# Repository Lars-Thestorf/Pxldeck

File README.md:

# Pxldeck

DIY Handheld Games Console with an 32x64 Led Matrix driven by ESP32.

The Display is an P3 HUB75 LedMatrix Module.
Lots of this Modules are usally used in Advertisement Panels.
The Case is entirely 3D printed.

## Features
- 32x64 pixel screen which can be stupidly bright
- 15 buttons and two analog sticks as input
- 3000mAh battery which lasts like 10 hours
- ESP32 microcontroller providing WiFi Capabilitys, does all the gameplay processing and is driving the Screen
- ATXMega microcontroller doing battery management and input handling since the ESP just hasn't enough pins for all of that. It also serves as an USB to Uart converter so the consoles software can be updated just by plugging it into the PC.
- This Repo also contains an "Emulator" to run the games code on PC.

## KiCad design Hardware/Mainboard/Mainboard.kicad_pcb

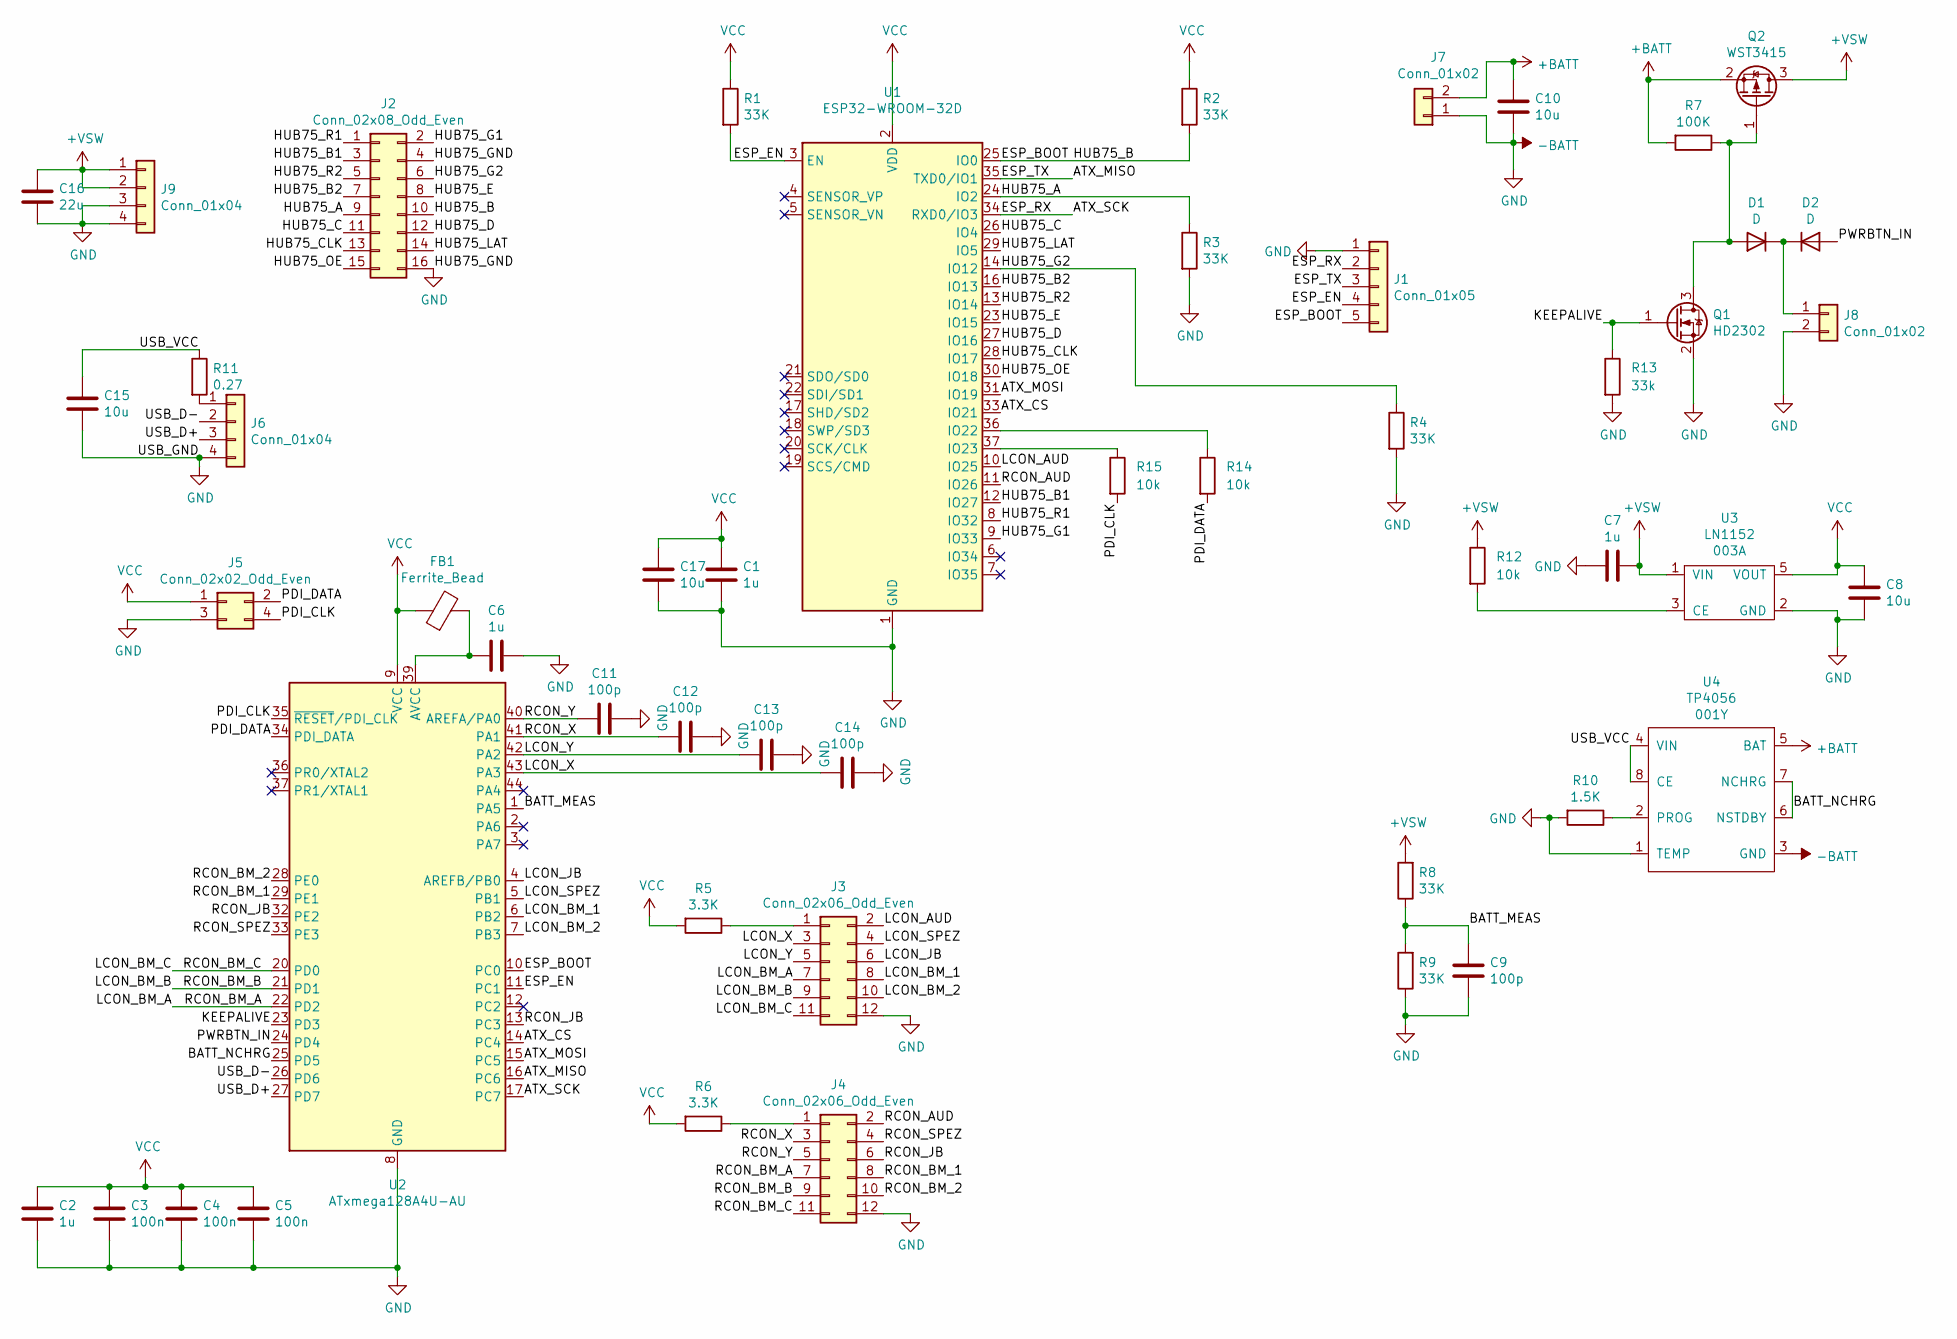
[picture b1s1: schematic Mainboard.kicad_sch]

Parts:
C1, C2, C6, C7: 1u; C_0402_1005Metric
C3, C4, C5: 100n; C_0402_1005Metric
C8: 10u; C_0805_2012Metric
C9, C11, C12, C13, C14: 100p; C_0402_1005Metric
C10, C15: 10u; C_0603_1608Metric
C16: 22u; C_1206_3216Metric
C17: 10u; C_1210_3225Metric
D1, D2: D; D_0603_1608Metric
FB1: Ferrite_Bead; L_0603_1608Metric
J1: Conn_01x05; PinHeader_1x05_P1.27mm_Vertical
J2: Conn_02x08_Odd_Even; PinSocket_2x08_P2.54mm_Vertical
J3, J4: Conn_02x06_Odd_Even; PinHeader_2x06_P2.54mm_Horizontal
J5: Conn_02x02_Odd_Even; PinHeader_2x02_P2.54mm_Vertical
J6, J9: Conn_01x04; PinHeader_1x04_P2.54mm_Vertical
J7, J8: Conn_01x02; PinHeader_1x02_P2.54mm_Vertical
Q1: HD2302; SOT-23
Q2: WST3415; TSOT-23
R1, R2, R3, R4, R8, R9: 33K; R_0402_1005Metric
R5, R6: 3.3K; R_0402_1005Metric
R7: 100K; R_0402_1005Metric
R10: 1.5K; R_0402_1005Metric
R11: 0.27; R_0805_2012Metric
R12, R14, R15: 10k; R_0402_1005Metric
R13: 33k; R_0402_1005Metric
U1: ESP32-WROOM-32D; ESP32-WROOM-32E
U2: ATxmega128A4U-AU; TQFP-44_10x10mm_P0.8mm
U3: LN1152; SOT-23-5
U4: TP4056; HSOP-8-1EP_3.9x4.9mm_P1.27mm_EP2.41x3.1mm_ThermalVias

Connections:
+BATT: C10.1, J7.2, Q2.2 (S), R7.2, U4.5 (BAT)
+VSW: C7.1, C16.1, J9.1, J9.2, Q2.3 (D), R8.2, R12.1, U3.1 (VIN)
-BATT: C1.2, C2.2, C3.2, C4.2, C5.2, C6.1, C7.2, C8.2, C9.2, C10.2, C11.1, C12.1, C13.1, C14.1, C15.2, C16.2, C17.2, J1.1, J2.4, J2.16, J3.12, J4.12, J5.3, J6.4, J7.1, J8.2, J9.3, J9.4, Q1.2 (S), R3.2, R4.2, R9.1, R10.2, R13.2, U1.1 (GND), U1.15 (GND), U1.38 (GND), U1.39 (GND), U2.8 (GND), U2.18 (GND), U2.30 (GND), U2.38 (GND), U3.2 (GND), U4.1 (TEMP), U4.3 (GND), U4.9 (GND)
/ATX_CS: U1.33 (IO21), U2.14 (PC4)
/ATX_MISO: J1.3, U1.35 (TXD0/IO1), U2.16 (PC6)
/ATX_MOSI: U1.31 (IO19), U2.15 (PC5)
/ATX_SCK: J1.2, U1.34 (RXD0/IO3), U2.17 (PC7)
/BATT_MEAS: C9.1, R8.1, R9.2, U2.1 (PA5)
/BATT_NCHRG: U2.25 (PD5), U4.6 (NSTDBY), U4.7 (NCHRG)
/ESP_BOOT: J1.5, J2.10, R2.2, U1.25 (IO0), U2.10 (PC0)
/ESP_EN: J1.4, R1.2, U1.3 (EN), U2.11 (PC1)
/HUB75_A: J2.9, R3.1, U1.24 (IO2)
/HUB75_B1: J2.3, U1.12 (IO27)
/HUB75_B2: J2.7, U1.16 (IO13)
/HUB75_C: J2.11, U1.26 (IO4)
/HUB75_CLK: J2.13, U1.28 (IO17)
/HUB75_D: J2.12, U1.27 (IO16)
/HUB75_E: J2.8, U1.23 (IO15)
/HUB75_G1: J2.2, U1.9 (IO33)
/HUB75_G2: J2.6, R4.1, U1.14 (IO12)
/HUB75_LAT: J2.14, U1.29 (IO5)
/HUB75_OE: J2.15, U1.30 (IO18)
/HUB75_R1: J2.1, U1.8 (IO32)
/HUB75_R2: J2.5, U1.13 (IO14)
/KEEPALIVE: Q1.1 (G), R13.1, U2.23 (PD3)
/LCON_AUD: J3.2, U1.10 (IO25)
/LCON_BM_1: J3.8, U2.6 (PB2)
/LCON_BM_2: J3.10, U2.7 (PB3)
/LCON_BM_A: J3.7, J4.7, U2.22 (PD2)
/LCON_BM_B: J3.9, J4.9, U2.21 (PD1)
/LCON_BM_C: J3.11, J4.11, U2.20 (PD0)
/LCON_JB: J3.6, U2.4 (AREFB/PB0)
/LCON_SPEZ: J3.4, U2.5 (PB1)
/LCON_X: C14.2, J3.3, U2.43 (PA3)
/LCON_Y: C13.2, J3.5, U2.42 (PA2)
/PDI_CLK: J5.4, R15.2, U2.35 (~RESET/PDI_CLK)
/PDI_DATA: J5.2, R14.2, U2.34 (PDI_DATA)
/PWRBTN_IN: D2.2 (A), U2.24 (PD4)
/RCON_AUD: J4.2, U1.11 (IO26)
/RCON_BM_1: J4.8, U2.29 (PE1)
/RCON_BM_2: J4.10, U2.28 (PE0)
/RCON_JB: J4.6, U2.13 (PC3), U2.32 (PE2)
/RCON_SPEZ: J4.4, U2.33 (PE3)
/RCON_X: C12.2, J4.3, U2.41 (PA1)
/RCON_Y: C11.2, J4.5, U2.40 (AREFA/PA0)
/USB_D+: J6.3, U2.27 (PD7)
/USB_D-: J6.2, U2.26 (PD6)
/USB_VCC: C15.1, R11.1, U4.4 (VIN), U4.8 (CE)
unnamed: C6.2, FB1.2, U2.39 (AVCC)
unnamed: D1.1 (K), D2.1 (K), J8.1
unnamed: D1.2 (A), Q1.3 (D), Q2.1 (G), R7.1
unnamed: J3.1, R5.1
unnamed: J4.1, R6.1
unnamed: J6.1, R11.2
unnamed: R10.1, U4.2 (PROG)
unnamed: R14.1, U1.36 (IO22)
unnamed: R15.1, U1.37 (IO23)
unnamed: R12.2, U3.3 (CE)
VCC: C1.1, C2.1, C3.1, C4.1, C5.1, C8.1, C17.1, FB1.1, J5.1, R1.1, R2.1, R5.2, R6.2, U1.2 (VDD), U2.9 (VCC), U2.19 (VCC), U2.31 (VCC), U3.5 (VOUT)

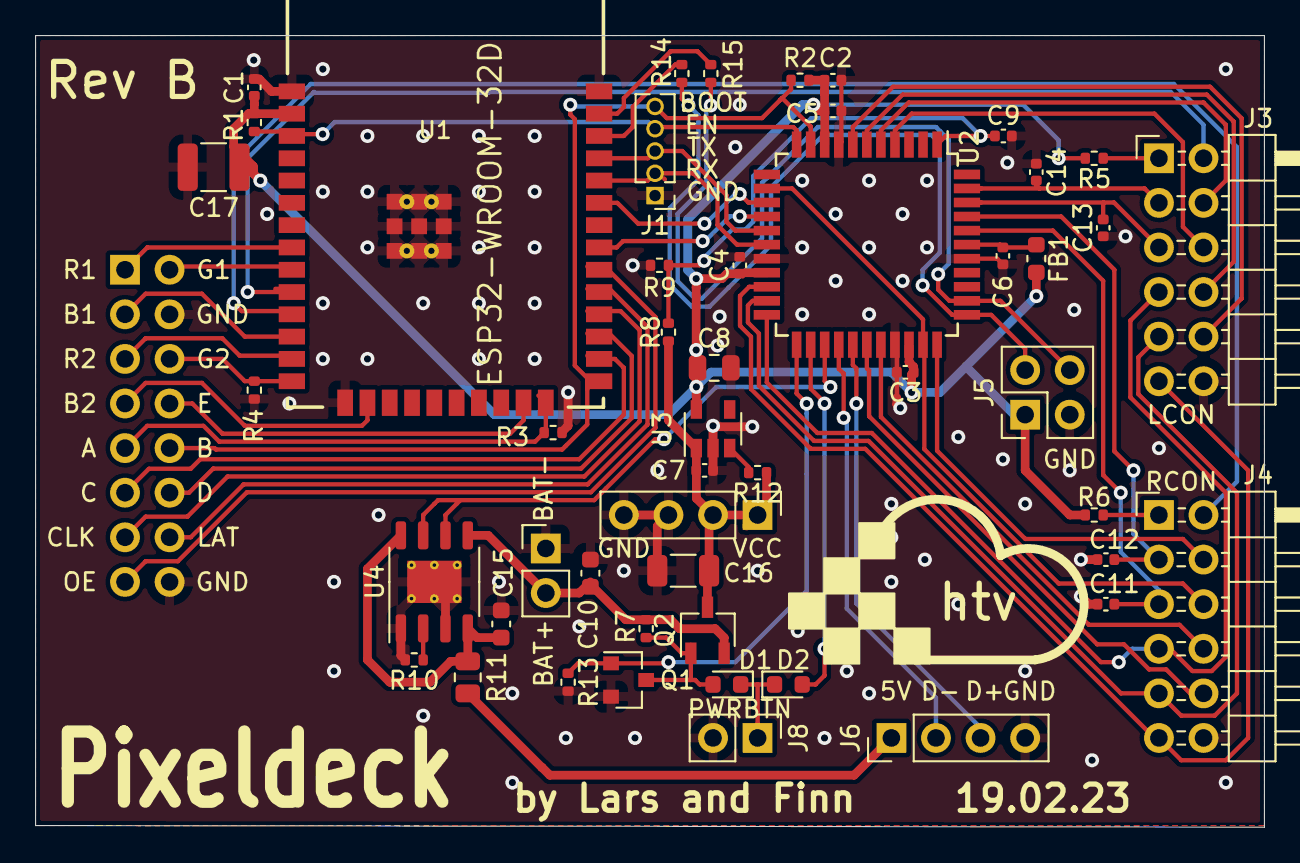
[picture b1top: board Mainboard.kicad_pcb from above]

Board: 2 copper layers, 70.0 x 45.1 mm, 50 parts (1 on the bottom side), 59 nets.

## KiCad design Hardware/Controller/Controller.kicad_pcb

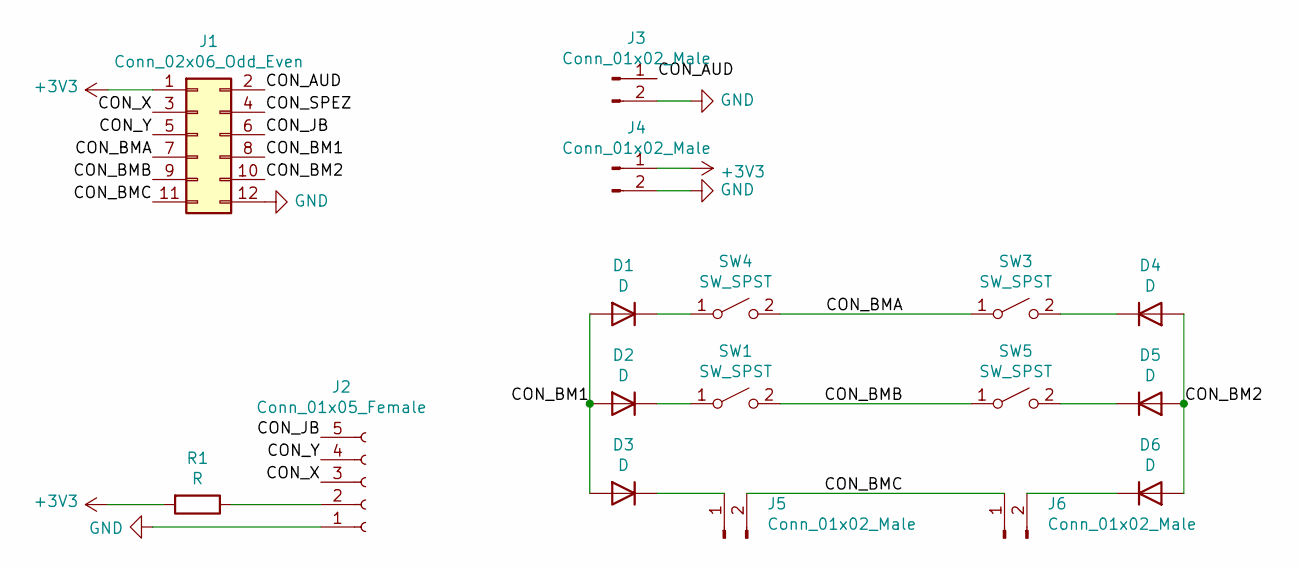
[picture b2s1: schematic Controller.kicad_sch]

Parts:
D1, D2, D3, D4, D5, D6: D; D_SOD-123
J1: Conn_02x06_Odd_Even; PinHeader_2x06_P2.54mm_Horizontal
J2: Conn_01x05_Female; PinSocket_1x05_P2.54mm_Horizontal
J3, J4: Conn_01x02_Male; PinHeader_1x02_P2.54mm_Vertical
J5, J6: Conn_01x02_Male; PinHeader_1x02_P2.54mm_Horizontal
R1: R; R_0402_1005Metric
SW1, SW3, SW4, SW5: SW_SPST; SW_SPST_B3S-1000

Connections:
+3V3: J1.1, J4.1, R1.2
/CON_AUD: J1.2, J3.1
/CON_BM1: D1.2 (A), D2.2 (A), D3.2 (A), J1.8
/CON_BM2: D4.2 (A), D5.2 (A), D6.2 (A), J1.10
/CON_BMA: J1.7, SW3.1 (A), SW4.2 (B)
/CON_BMB: J1.9, SW1.2 (B), SW5.1 (A)
/CON_BMC: J1.11, J5.2, J6.1
/CON_JB: J1.6, J2.5
/CON_SPEZ: J1.4
/CON_X: J1.3, J2.3
/CON_Y: J1.5, J2.4
GND: J1.12, J2.1, J3.2, J4.2
unnamed: D1.1 (K), SW4.1 (A)
unnamed: D2.1 (K), SW1.1 (A)
unnamed: D3.1 (K), J5.1
unnamed: D4.1 (K), SW3.2 (B)
unnamed: D5.1 (K), SW5.2 (B)
unnamed: D6.1 (K), J6.2
unnamed: J2.2, R1.1

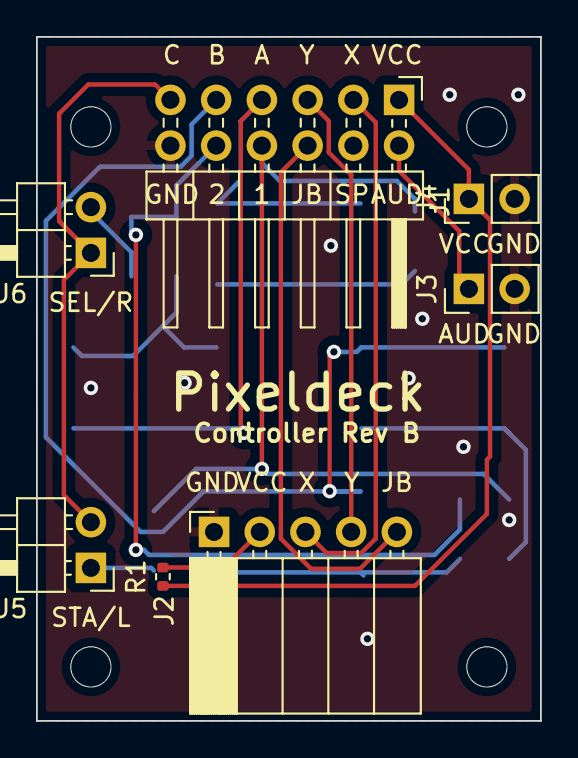
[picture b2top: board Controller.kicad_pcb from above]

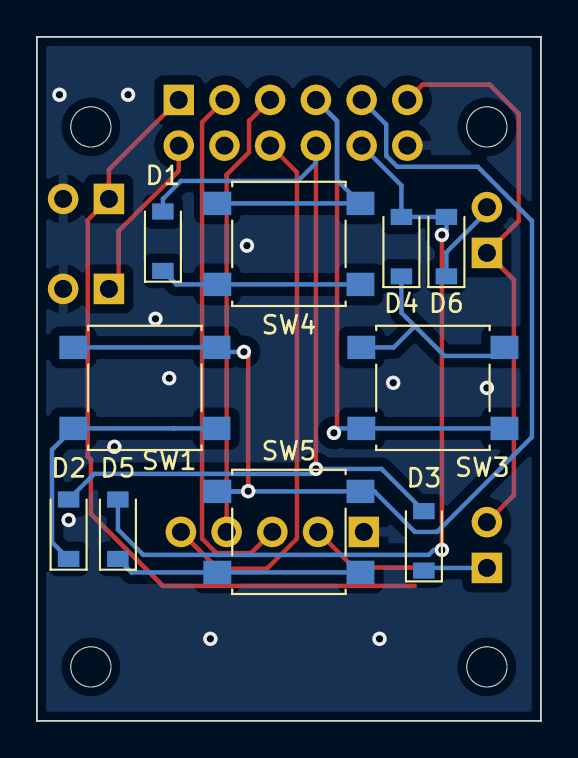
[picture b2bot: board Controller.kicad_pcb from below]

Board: 2 copper layers, 28.0 x 38.0 mm, 17 parts (10 on the bottom side), 18 nets.

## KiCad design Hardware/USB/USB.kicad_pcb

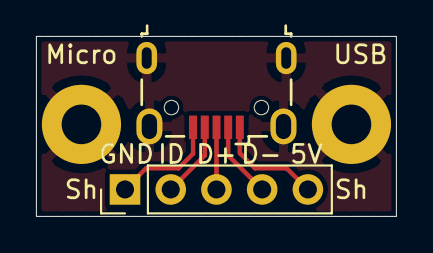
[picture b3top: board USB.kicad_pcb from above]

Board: 2 copper layers, 20.0 x 10.0 mm, 4 parts (0 on the bottom side), 6 nets.

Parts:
H1, H2: MountingHole_Pad; MountingHole_2.2mm_M2_Pad
J1: USB_OTG; USB_Micro-B_Wuerth_629105150521
J2: Conn_01x05_Male; PinHeader_1x05_P2.54mm_Vertical

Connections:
/5V: J1.1, J2.5
/D+: J1.3, J2.3
/D-: J1.2, J2.4
/GND: J1.5, J2.1
/ID: J1.4, J2.2
/Shield: H1.1, H2.1, J1.6

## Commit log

2021-08-07 Initial commit2
2021-08-08 power management
2021-08-10 finetuning
2021-08-10 fixing
2021-08-15 Mainboard finished?
2021-08-16 more powerfull main pfet
2021-09-04 add case and code
2021-09-05 bootlogo
2021-09-06 xmega as hackyprog
2021-09-10 xmega software
2021-09-11 uart comm
2021-09-12 button comm working
2021-09-12 kleinigkeit
2021-09-15 first working state of main menu
2021-09-18 first working state with pong
2021-09-18 new power button interrupt
2021-09-21 fix USB issues
2021-09-25 make pong more fun and joystick calibration
2021-09-27 draw Image function
2021-09-27 make lufa an actual submodule
2021-09-29 Multiplayer
2021-10-08 Teeetrrriiiiisss
2021-10-10 better tetris
2021-11-15 Add controller PCB
2021-11-19 highscore list
2021-11-21 Changes related to new Controller pcb#
2021-12-18 start refactoring for getting emulator to work
2021-12-19 still hacky but working tetris on emu
2021-12-24 worked on porting
2022-01-15 add sokoban game
2022-01-15 small sokoban bugfix update
2022-08-05 sokoban bugfixes, attempt flimmer reduction
2022-11-10 lots of rework on HMatrix software architecture
2022-12-11 new button tolerances
2022-12-11 Add README.md
2023-01-07 add power button to case
2023-01-18 snake
2023-01-20 websocketserver, not working yet
2023-01-21 wifi starts webserver not wörking
2023-01-31 wie viele Sokuban Level willst du? - Ja. xD
2023-01-31 small Sokoban changes
2023-01-31 Lars will alten progress fix
2023-01-31 bug vielleicht gefixt
2023-01-31 add game icons
2023-02-01 green border when soko world finisched
2023-02-01 andere Variante für websocketserver. Irgendwas mit cmake falsch. Komponente wird erkannt und gebaut, hab aber eine undifined reference. Komponente wird nicht in die main gelinked. Weis nicht wie man 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
2023-02-01 add highscore to tetris
2023-02-02 Tetris auch mit A startbar
2023-02-04 change playerinput. Emulator changes for playerinput needed
2023-02-04 settingsmenu
2023-02-05 fix emulator and new input handling
2023-02-05 fix redshift and brightness settings
2023-02-05 Nach homebutton press, wird nicht menü geöffnet
2023-02-06 Accounts gehen soweit. Emulator braucht 2 storage Funktionen für Strings. Finn hat schon wieder Emulator zerstört. :/
2023-02-07 Higscores in Tetris mit namen! Merkwürdiger bug. Speichert nur namen bis 2 zeichen oder kann nur namen mit 2 zeichen lesen
2023-02-07 weiter probiert,aber gelicher Felher. bin ratlos
2023-02-07 implement string storage functions for emulator
2023-02-07 sankegame step to mp
2023-02-09 i dont know
2023-02-10 start working on tetris multiplayer
2023-02-12 change tetris structure
2023-02-12 tetris multiplayer almost playable
2023-02-14 start to implement rotation
2023-02-19 rev 2 Hw
2023-03-23 Rename Project in readme
2023-04-02 improve controller stability
2023-04-08 StartSelectPlate
2023-04-09 added and fixed startselect button holder
2024-01-04 Add Multiplayer Api and a multiplayer multiconsole TicTacToe to test it
2024-01-24 fix tetris on emulator
2024-02-18 fix tetris highscore bug and multiplayer screen offset
2025-02-17 better sokoban level select and other small improvements
